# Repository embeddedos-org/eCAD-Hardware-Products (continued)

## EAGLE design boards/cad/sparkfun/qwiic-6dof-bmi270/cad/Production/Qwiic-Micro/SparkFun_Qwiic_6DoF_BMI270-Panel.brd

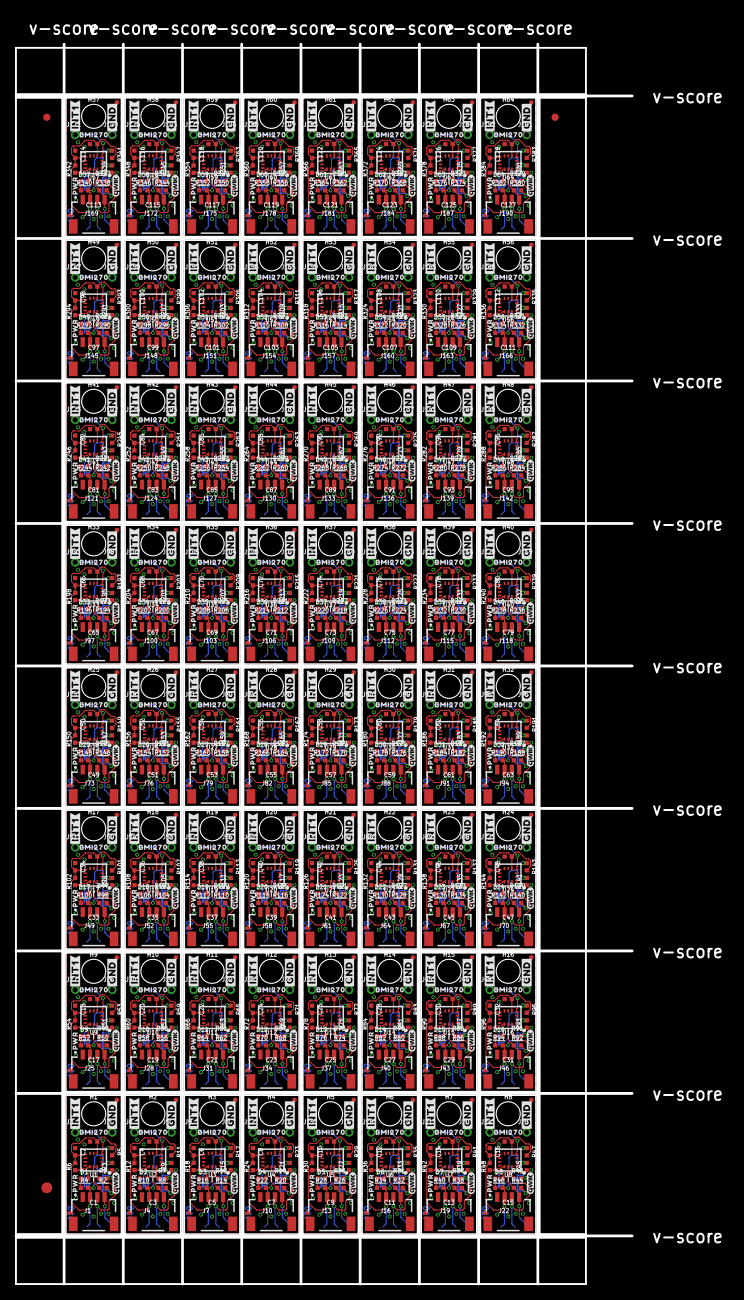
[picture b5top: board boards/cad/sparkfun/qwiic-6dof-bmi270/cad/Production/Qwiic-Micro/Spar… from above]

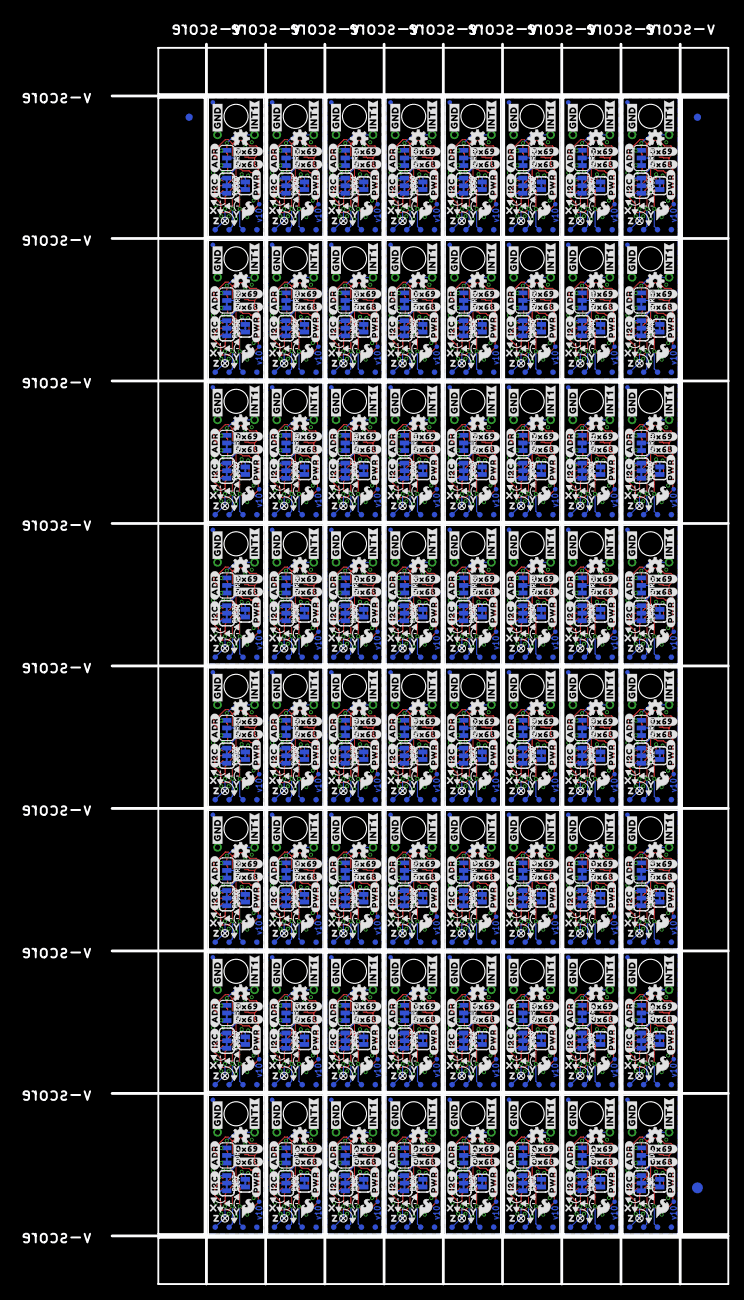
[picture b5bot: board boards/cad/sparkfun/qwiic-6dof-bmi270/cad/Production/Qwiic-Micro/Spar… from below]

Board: 2 copper layers, 84.6 x 170.2 mm, 2822 parts (1411 on the bottom side), 832 nets.

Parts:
ADR, ADR1, ADR2, ADR3, ADR4, ADR5, ADR6, ADR7, ADR8, ADR9, ADR10, ADR11, ADR12, ADR13, ADR14, ADR15, ADR16, ADR17, ADR18, ADR19, ADR20, ADR21, ADR22, ADR23, ADR24, ADR25, ADR26, ADR27, ADR28, ADR29, ADR30, ADR31, ADR32, ADR33, ADR34, ADR35, ADR36, ADR37, ADR38, ADR39, ADR40, ADR41, ADR42, ADR43, ADR44, ADR45, ADR46, ADR47, ADR48, ADR49, ADR50, ADR51, ADR52, ADR53, ADR54, ADR55, ADR56, ADR57, ADR58, ADR59, ADR60, ADR61, ADR62, ADR63: JUMPER-SMT_3_1-NC_TRACE_SILK; SMT-JUMPER_3_1-NC_TRACE_SILK
C1, C2, C3, C4, C5, C6, C7, C8, C9, C10, C11, C12, C13, C14, C15, C16, C17, C18, C19, C20, C21, C22, C23, C24, C25, C26, C27, C28, C29, C30, C31, C32, C33, C34, C35, C36, C37, C38, C39, C40, C41, C42, C43, C44, C45, C46, C47, C48, C49, C50, C51, C52, C53, C54, C55, C56, C57, C58, C59, C60, C61, C62, C63, C64, C65, C66, C67, C68, C69, C70, C71, C72, C73, C74, C75, C76, C77, C78, C79, C80, C81, C82, C83, C84, C85, C86, C87, C88, C89, C90, C91, C92, C93, C94, C95, C96, C97, C98, C99, C100, C101, C102, C103, C104, C105, C106, C107, C108, C109, C110, C111, C112, C113, C114, C115, C116, C117, C118, C119, C120, C121, C122, C123, C124, C125, C126, C127, C128: 0.1uF; 0402-TIGHT
D1, D2, D3, D4, D5, D6, D7, D8, D9, D10, D11, D12, D13, D14, D15, D16, D17, D18, D19, D20, D21, D22, D23, D24, D25, D26, D27, D28, D29, D30, D31, D32, D33, D34, D35, D36, D37, D38, D39, D40, D41, D42, D43, D44, D45, D46, D47, D48, D49, D50, D51, D52, D53, D54, D55, D56, D57, D58, D59, D60, D61, D62, D63, D64: RED; LED-0402
E$1, E$2, E$3, E$4: FIDUCIAL-1X2
E$5, E$6: FIDUCIAL-1.5X3
FD1, FD2, FD3, FD4, FD5, FD6, FD7, FD8, FD9, FD10, FD11, FD12, FD13, FD14, FD15, FD16, FD17, FD18, FD19, FD20, FD21, FD22, FD23, FD24, FD25, FD26, FD27, FD28, FD29, FD30, FD31, FD32, FD33, FD34, FD35, FD36, FD37, FD38, FD39, FD40, FD41, FD42, FD43, FD44, FD45, FD46, FD47, FD48, FD49, FD50, FD51, FD52, FD53, FD54, FD55, FD56, FD57, FD58, FD59, FD60, FD61, FD62, FD63, FD64, FD65, FD66, FD67, FD68, FD69, FD70, FD71, FD72, FD73, FD74, FD75, FD76, FD77, FD78, FD79, FD80, FD81, FD82, FD83, FD84, FD85, FD86, FD87, FD88, FD89, FD90, FD91, FD92, FD93, FD94, FD95, FD96, FD97, FD98, FD99, FD100, FD101, FD102, FD103, FD104, FD105, FD106, FD107, FD108, FD109, FD110, FD111, FD112, FD113, FD114, FD115, FD116, FD117, FD118, FD119, FD120, FD121, FD122, FD123, FD124, FD125, FD126, FD127, FD128, FD129, FD130, FD131, FD132, FD133, FD134, FD135, FD136, FD137, FD138, FD139, FD140, FD141, FD142, FD143, FD144, FD145, FD146, FD147, FD148, FD149, FD150, FD151, FD152, FD153, FD154, FD155, FD156, FD157, FD158, FD159, FD160, FD161, FD162, FD163, FD164, FD165, FD166, FD167, FD168, FD169, FD170, FD171, FD172, FD173, FD174, FD175, FD176, FD177, FD178, FD179, FD180, FD181, FD182, FD183, FD184, FD185, FD186, FD187, FD188, FD189, FD190, FD191, FD192, FD193, FD194, FD195, FD196, FD197, FD198, FD199, FD200, FD201, FD202, FD203, FD204, FD205, FD206, FD207, FD208, FD209, FD210, FD211, FD212, FD213, FD214, FD215, FD216, FD217, FD218, FD219, FD220, FD221, FD222, FD223, FD224, FD225, FD226, FD227, FD228, FD229, FD230, FD231, FD232, FD233, FD234, FD235, FD236, FD237, FD238, FD239, FD240, FD241, FD242, FD243, FD244, FD245, FD246, FD247, FD248, FD249, FD250, FD251, FD252, FD253, FD254, FD255, FD256: FIDUCIALUFIDUCIAL; FIDUCIAL-MICRO
FRAME1, FRAME2, FRAME3, FRAME4, FRAME5, FRAME6, FRAME7, FRAME8, FRAME9, FRAME10, FRAME11, FRAME12, FRAME13, FRAME14, FRAME15, FRAME16, FRAME17, FRAME18, FRAME19, FRAME20, FRAME21, FRAME22, FRAME23, FRAME24, FRAME25, FRAME26, FRAME27, FRAME28, FRAME29, FRAME30, FRAME31, FRAME32, FRAME33, FRAME34, FRAME35, FRAME36, FRAME37, FRAME38, FRAME39, FRAME40, FRAME41, FRAME42, FRAME43, FRAME44, FRAME45, FRAME46, FRAME47, FRAME48, FRAME49, FRAME50, FRAME51, FRAME52, FRAME53, FRAME54, FRAME55, FRAME56, FRAME57, FRAME58, FRAME59, FRAME60, FRAME61, FRAME62, FRAME63, FRAME64: FRAME-LETTER; CREATIVE_COMMONS
H1, H2, H3, H4, H5, H6, H7, H8, H9, H10, H11, H12, H13, H14, H15, H16, H17, H18, H19, H20, H21, H22, H23, H24, H25, H26, H27, H28, H29, H30, H31, H32, H33, H34, H35, H36, H37, H38, H39, H40, H41, H42, H43, H44, H45, H46, H47, H48, H49, H50, H51, H52, H53, H54, H55, H56, H57, H58, H59, H60, H61, H62, H63, H64: STAND-OFF
I2C, I2C1, I2C2, I2C3, I2C4, I2C5, I2C6, I2C7, I2C8, I2C9, I2C10, I2C11, I2C12, I2C13, I2C14, I2C15, I2C16, I2C17, I2C18, I2C19, I2C20, I2C21, I2C22, I2C23, I2C24, I2C25, I2C26, I2C27, I2C28, I2C29, I2C30, I2C31, I2C32, I2C33, I2C34, I2C35, I2C36, I2C37, I2C38, I2C39, I2C40, I2C41, I2C42, I2C43, I2C44, I2C45, I2C46, I2C47, I2C48, I2C49, I2C50, I2C51, I2C52, I2C53, I2C54, I2C55, I2C56, I2C57, I2C58, I2C59, I2C60, I2C61, I2C62, I2C63: JUMPER-SMT_3_2-NC_TRACE_SILK; SMT-JUMPER_3_2-NC_TRACE_SILK
J1, J4, J7, J10, J13, J16, J19, J22, J25, J28, J31, J34, J37, J40, J43, J46, J49, J52, J55, J58, J61, J64, J67, J70, J73, J76, J79, J82, J85, J88, J91, J94, J97, J100, J103, J106, J109, J112, J115, J118, J121, J124, J127, J130, J133, J136, J139, J142, J145, J148, J151, J154, J157, J160, J163, J166, J169, J172, J175, J178, J181, J184, J187, J190: QWIIC_RIGHT_ANGLE; JST04_1MM_RA
J2, J3, J5, J6, J8, J9, J11, J12, J14, J15, J17, J18, J20, J21, J23, J24, J26, J27, J29, J30, J32, J33, J35, J36, J38, J39, J41, J42, J44, J45, J47, J48, J50, J51, J53, J54, J56, J57, J59, J60, J62, J63, J65, J66, J68, J69, J71, J72, J74, J75, J77, J78, J80, J81, J83, J84, J86, J87, J89, J90, J92, J93, J95, J96, J98, J99, J101, J102, J104, J105, J107, J108, J110, J111, J113, J114, J116, J117, J119, J120, J122, J123, J125, J126, J128, J129, J131, J132, J134, J135, J137, J138, J140, J141, J143, J144, J146, J147, J149, J150, J152, J153, J155, J156, J158, J159, J161, J162, J164, J165, J167, J168, J170, J171, J173, J174, J176, J177, J179, J180, J182, J183, J185, J186, J188, J189, J191, J192: 1X01_1MM_NO_SILK
LOGO1, LOGO4, LOGO7, LOGO10, LOGO13, LOGO16, LOGO19, LOGO22, LOGO25, LOGO28, LOGO31, LOGO34, LOGO37, LOGO40, LOGO43, LOGO46, LOGO49, LOGO52, LOGO55, LOGO58, LOGO61, LOGO64, LOGO67, LOGO70, LOGO73, LOGO76, LOGO79, LOGO82, LOGO85, LOGO88, LOGO91, LOGO94, LOGO97, LOGO100, LOGO103, LOGO106, LOGO109, LOGO112, LOGO115, LOGO118, LOGO121, LOGO124, LOGO127, LOGO130, LOGO133, LOGO136, LOGO139, LOGO142, LOGO145, LOGO148, LOGO151, LOGO154, LOGO157, LOGO160, LOGO163, LOGO166, LOGO169, LOGO172, LOGO175, LOGO178, LOGO181, LOGO184, LOGO187, LOGO190: SFE_LOGO_NAME_FLAMEBLANK; BLANK
LOGO2, LOGO5, LOGO8, LOGO11, LOGO14, LOGO17, LOGO20, LOGO23, LOGO26, LOGO29, LOGO32, LOGO35, LOGO38, LOGO41, LOGO44, LOGO47, LOGO50, LOGO53, LOGO56, LOGO59, LOGO62, LOGO65, LOGO68, LOGO71, LOGO74, LOGO77, LOGO80, LOGO83, LOGO86, LOGO89, LOGO92, LOGO95, LOGO98, LOGO101, LOGO104, LOGO107, LOGO110, LOGO113, LOGO116, LOGO119, LOGO122, LOGO125, LOGO128, LOGO131, LOGO134, LOGO137, LOGO140, LOGO143, LOGO146, LOGO149, LOGO152, LOGO155, LOGO158, LOGO161, LOGO164, LOGO167, LOGO170, LOGO173, LOGO176, LOGO179, LOGO182, LOGO185, LOGO188, LOGO191: QWIIC_LOGO_3MM; QWIIC_3MM
LOGO3, LOGO6, LOGO9, LOGO12, LOGO15, LOGO18, LOGO21, LOGO24, LOGO27, LOGO30, LOGO33, LOGO36, LOGO39, LOGO42, LOGO45, LOGO48, LOGO51, LOGO54, LOGO57, LOGO60, LOGO63, LOGO66, LOGO69, LOGO72, LOGO75, LOGO78, LOGO81, LOGO84, LOGO87, LOGO90, LOGO93, LOGO96, LOGO99, LOGO102, LOGO105, LOGO108, LOGO111, LOGO114, LOGO117, LOGO120, LOGO123, LOGO126, LOGO129, LOGO132, LOGO135, LOGO138, LOGO141, LOGO144, LOGO147, LOGO150, LOGO153, LOGO156, LOGO159, LOGO162, LOGO165, LOGO168, LOGO171, LOGO174, LOGO177, LOGO180, LOGO183, LOGO186, LOGO189, LOGO192: OSHW-LOGOMINI; OSHW-LOGO-MINI
PWR, PWR1, PWR2, PWR3, PWR4, PWR5, PWR6, PWR7, PWR8, PWR9, PWR10, PWR11, PWR12, PWR13, PWR14, PWR15, PWR16, PWR17, PWR18, PWR19, PWR20, PWR21, PWR22, PWR23, PWR24, PWR25, PWR26, PWR27, PWR28, PWR29, PWR30, PWR31, PWR32, PWR33, PWR34, PWR35, PWR36, PWR37, PWR38, PWR39, PWR40, PWR41, PWR42, PWR43, PWR44, PWR45, PWR46, PWR47, PWR48, PWR49, PWR50, PWR51, PWR52, PWR53, PWR54, PWR55, PWR56, PWR57, PWR58, PWR59, PWR60, PWR61, PWR62, PWR63: JUMPER-SMT_2_NC_TRACE_SILK; SMT-JUMPER_2_NC_TRACE_SILK
R1, R2, R7, R8, R13, R14, R19, R20, R25, R26, R31, R32, R37, R38, R43, R44, R49, R50, R55, R56, R61, R62, R67, R68, R73, R74, R79, R80, R85, R86, R91, R92, R97, R98, R103, R104, R109, R110, R115, R116, R121, R122, R127, R128, R133, R134, R139, R140, R145, R146, R151, R152, R157, R158, R163, R164, R169, R170, R175, R176, R181, R182, R187, R188, R193, R194, R199, R200, R205, R206, R211, R212, R217, R218, R223, R224, R229, R230, R235, R236, R241, R242, R247, R248, R253, R254, R259, R260, R265, R266, R271, R272, R277, R278, R283, R284, R289, R290, R295, R296, R301, R302, R307, R308, R313, R314, R319, R320, R325, R326, R331, R332, R337, R338, R343, R344, R349, R350, R355, R356, R361, R362, R367, R368, R373, R374, R379, R380: 2.2k; 0402-TIGHT
R3, R5, R6, R9, R11, R12, R15, R17, R18, R21, R23, R24, R27, R29, R30, R33, R35, R36, R39, R41, R42, R45, R47, R48, R51, R53, R54, R57, R59, R60, R63, R65, R66, R69, R71, R72, R75, R77, R78, R81, R83, R84, R87, R89, R90, R93, R95, R96, R99, R101, R102, R105, R107, R108, R111, R113, R114, R117, R119, R120, R123, R125, R126, R129, R131, R132, R135, R137, R138, R141, R143, R144, R147, R149, R150, R153, R155, R156, R159, R161, R162, R165, R167, R168, R171, R173, R174, R177, R179, R180, R183, R185, R186, R189, R191, R192, R195, R197, R198, R201, R203, R204, R207, R209, R210, R213, R215, R216, R219, R221, R222, R225, R227, R228, R231, R233, R234, R237, R239, R240, R243, R245, R246, R249, R251, R252, R255, R257, R258, R261, R263, R264, R267, R269, R270, R273, R275, R276, R279, R281, R282, R285, R287, R288, R291, R293, R294, R297, R299, R300, R303, R305, R306, R309, R311, R312, R315, R317, R318, R321, R323, R324, R327, R329, R330, R333, R335, R336, R339, R341, R342, R345, R347, R348, R351, R353, R354, R357, R359, R360, R363, R365, R366, R369, R371, R372, R375, R377, R378, R381, R383, R384: 100k; 0402-TIGHT
R4, R10, R16, R22, R28, R34, R40, R46, R52, R58, R64, R70, R76, R82, R88, R94, R100, R106, R112, R118, R124, R130, R136, R142, R148, R154, R160, R166, R172, R178, R184, R190, R196, R202, R208, R214, R220, R226, R232, R238, R244, R250, R256, R262, R268, R274, R280, R286, R292, R298, R304, R310, R316, R322, R328, R334, R340, R346, R352, R358, R364, R370, R376, R382: 4.7k; 0402-TIGHT
TP1, TP2, TP3, TP4, TP5, TP6, TP7, TP8, TP9, TP10, TP11, TP12, TP13, TP14, TP15, TP16, TP17, TP18, TP19, TP20, TP21, TP22, TP23, TP24, TP25, TP26, TP27, TP28, TP29, TP30, TP31, TP32, TP33, TP34, TP35, TP36, TP37, TP38, TP39, TP40, TP41, TP42, TP43, TP44, TP45, TP46, TP47, TP48, TP49, TP50, TP51, TP52, TP53, TP54, TP55, TP56, TP57, TP58, TP59, TP60, TP61, TP62, TP63, TP64, TP65, TP66, TP67, TP68, TP69, TP70, TP71, TP72, TP73, TP74, TP75, TP76, TP77, TP78, TP79, TP80, TP81, TP82, TP83, TP84, TP85, TP86, TP87, TP88, TP89, TP90, TP91, TP92, TP93, TP94, TP95, TP96, TP97, TP98, TP99, TP100, TP101, TP102, TP103, TP104, TP105, TP106, TP107, TP108, TP109, TP110, TP111, TP112, TP113, TP114, TP115, TP116, TP117, TP118, TP119, TP120, TP121, TP122, TP123, TP124, TP125, TP126, TP127, TP128, TP129, TP130, TP131, TP132, TP133, TP134, TP135, TP136, TP137, TP138, TP139, TP140, TP141, TP142, TP143, TP144, TP145, TP146, TP147, TP148, TP149, TP150, TP151, TP152, TP153, TP154, TP155, TP156, TP157, TP158, TP159, TP160, TP161, TP162, TP163, TP164, TP165, TP166, TP167, TP168, TP169, TP170, TP171, TP172, TP173, TP174, TP175, TP176, TP177, TP178, TP179, TP180, TP181, TP182, TP183, TP184, TP185, TP186, TP187, TP188, TP189, TP190, TP191, TP192, TP193, TP194, TP195, TP196, TP197, TP198, TP199, TP200, TP201, TP202, TP203, TP204, TP205, TP206, TP207, TP208, TP209, TP210, TP211, TP212, TP213, TP214, TP215, TP216, TP217, TP218, TP219, TP220, TP221, TP222, TP223, TP224, TP225, TP226, TP227, TP228, TP229, TP230, TP231, TP232, TP233, TP234, TP235, TP236, TP237, TP238, TP239, TP240, TP241, TP242, TP243, TP244, TP245, TP246, TP247, TP248, TP249, TP250, TP251, TP252, TP253, TP254, TP255, TP256: TEST-POINT3; PAD.03X.03
U1, U2, U3, U4, U5, U6, U7, U8, U9, U10, U11, U12, U13, U14, U15, U16, U17, U18, U19, U20, U21, U22, U23, U24, U25, U26, U27, U28, U29, U30, U31, U32, U33, U34, U35, U36, U37, U38, U39, U40, U41, U42, U43, U44, U45, U46, U47, U48, U49, U50, U51, U52, U53, U54, U55, U56, U57, U58, U59, U60, U61, U62, U63, U64: BMI270
U$1, U$10, U$27, U$43, U$58, U$73, U$91, U$106, U$121, U$136, U$151, U$166, U$181, U$196, U$211, U$226, U$241, U$256, U$271, U$286, U$301, U$316, U$331, U$346, U$361, U$376, U$391, U$406, U$421, U$436, U$451, U$466, U$481, U$496, U$511, U$526, U$541, U$556, U$571, U$586, U$601, U$616, U$631, U$646, U$661, U$676, U$691, U$706, U$721, U$736, U$751, U$766, U$781, U$796, U$811, U$826, U$841, U$856, U$871, U$886, U$901, U$916, U$931, U$946: #I2C#0
U$2, U$7, U$22, U$23, U$38, U$39, U$53, U$54, U$68, U$69, U$86, U$87, U$101, U$102, U$116, U$117, U$131, U$132, U$146, U$147, U$161, U$162, U$176, U$177, U$191, U$192, U$206, U$207, U$221, U$222, U$236, U$237, U$251, U$252, U$266, U$267, U$281, U$282, U$296, U$297, U$311, U$312, U$326, U$327, U$341, U$342, U$356, U$357, U$371, U$372, U$386, U$387, U$401, U$402, U$416, U$417, U$431, U$432, U$446, U$447, U$461, U$462, U$476, U$477, U$491, U$492, U$506, U$507, U$521, U$522, U$536, U$537, U$551, U$552, U$566, U$567, U$581, U$582, U$596, U$597, U$611, U$612, U$626, U$627, U$641, U$642, U$656, U$657, U$671, U$672, U$686, U$687, U$701, U$702, U$716, U$717, U$731, U$732, U$746, U$747, U$761, U$762, U$776, U$777, U$791, U$792, U$806, U$807, U$821, U$822, U$836, U$837, U$851, U$852, U$866, U$867, U$881, U$882, U$896, U$897, U$911, U$912, U$926, U$927, U$941, U$942, U$956, U$957: #GND#0
U$3, U$26, U$42, U$57, U$72, U$90, U$105, U$120, U$135, U$150, U$165, U$180, U$195, U$210, U$225, U$240, U$255, U$270, U$285, U$300, U$315, U$330, U$345, U$360, U$375, U$390, U$405, U$420, U$435, U$450, U$465, U$480, U$495, U$510, U$525, U$540, U$555, U$570, U$585, U$600, U$615, U$630, U$645, U$660, U$675, U$690, U$705, U$720, U$735, U$750, U$765, U$780, U$795, U$810, U$825, U$840, U$855, U$870, U$885, U$900, U$915, U$930, U$945, U$960: SFE_LOGO_FLAME_.1
U$4, U$11, U$28, U$44, U$59, U$74, U$92, U$107, U$122, U$137, U$152, U$167, U$182, U$197, U$212, U$227, U$242, U$257, U$272, U$287, U$302, U$317, U$332, U$347, U$362, U$377, U$392, U$407, U$422, U$437, U$452, U$467, U$482, U$497, U$512, U$527, U$542, U$557, U$572, U$587, U$602, U$617, U$632, U$647, U$662, U$677, U$692, U$707, U$722, U$737, U$752, U$767, U$782, U$797, U$812, U$827, U$842, U$857, U$872, U$887, U$902, U$917, U$932, U$947: #PWR#0
U$5, U$12, U$29, U$45, U$60, U$75, U$93, U$108, U$123, U$138, U$153, U$168, U$183, U$198, U$213, U$228, U$243, U$258, U$273, U$288, U$303, U$318, U$333, U$348, U$363, U$378, U$393, U$408, U$423, U$438, U$453, U$468, U$483, U$498, U$513, U$528, U$543, U$558, U$573, U$588, U$603, U$618, U$633, U$648, U$663, U$678, U$693, U$708, U$723, U$738, U$753, U$768, U$783, U$798, U$813, U$828, U$843, U$858, U$873, U$888, U$903, U$918, U$933, U$948: #ADR#0
U$6, U$13, U$30, U$46, U$61, U$76, U$94, U$109, U$124, U$139, U$154, U$169, U$184, U$199, U$214, U$229, U$244, U$259, U$274, U$289, U$304, U$319, U$334, U$349, U$364, U$379, U$394, U$409, U$424, U$439, U$454, U$469, U$484, U$499, U$514, U$529, U$544, U$559, U$574, U$589, U$604, U$619, U$634, U$649, U$664, U$679, U$694, U$709, U$724, U$739, U$754, U$769, U$784, U$799, U$814, U$829, U$844, U$859, U$874, U$889, U$904, U$919, U$934, U$949: #0X68#0
U$8, U$9, U$24, U$25, U$40, U$41, U$55, U$56, U$70, U$71, U$88, U$89, U$103, U$104, U$118, U$119, U$133, U$134, U$148, U$149, U$163, U$164, U$178, U$179, U$193, U$194, U$208, U$209, U$223, U$224, U$238, U$239, U$253, U$254, U$268, U$269, U$283, U$284, U$298, U$299, U$313, U$314, U$328, U$329, U$343, U$344, U$358, U$359, U$373, U$374, U$388, U$389, U$403, U$404, U$418, U$419, U$433, U$434, U$448, U$449, U$463, U$464, U$478, U$479, U$493, U$494, U$508, U$509, U$523, U$524, U$538, U$539, U$553, U$554, U$568, U$569, U$583, U$584, U$598, U$599, U$613, U$614, U$628, U$629, U$643, U$644, U$658, U$659, U$673, U$674, U$688, U$689, U$703, U$704, U$718, U$719, U$733, U$734, U$748, U$749, U$763, U$764, U$778, U$779, U$793, U$794, U$808, U$809, U$823, U$824, U$838, U$839, U$853, U$854, U$868, U$869, U$883, U$884, U$898, U$899, U$913, U$914, U$928, U$929, U$943, U$944, U$958, U$959: #INT1#0
U$14, U$18, U$31, U$47, U$62, U$77, U$95, U$110, U$125, U$140, U$155, U$170, U$185, U$200, U$215, U$230, U$245, U$260, U$275, U$290, U$305, U$320, U$335, U$350, U$365, U$380, U$395, U$410, U$425, U$440, U$455, U$470, U$485, U$500, U$515, U$530, U$545, U$560, U$575, U$590, U$605, U$620, U$635, U$650, U$665, U$680, U$695, U$710, U$725, U$740, U$755, U$770, U$785, U$800, U$815, U$830, U$845, U$860, U$875, U$890, U$905, U$920, U$935, U$950: #0X69#0
U$15, U$21, U$32, U$48, U$63, U$78, U$96, U$111, U$126, U$141, U$156, U$171, U$186, U$201, U$216, U$231, U$246, U$261, U$276, U$291, U$306, U$321, U$336, U$351, U$366, U$381, U$396, U$411, U$426, U$441, U$456, U$471, U$486, U$501, U$516, U$531, U$546, U$561, U$576, U$591, U$606, U$621, U$636, U$651, U$666, U$681, U$696, U$711, U$726, U$741, U$756, U$771, U$786, U$801, U$816, U$831, U$846, U$861, U$876, U$891, U$906, U$921, U$936, U$951: BMI2700
U$16, U$33, U$49, U$64, U$79, U$82, U$97, U$112, U$127, U$142, U$157, U$172, U$187, U$202, U$217, U$232, U$247, U$262, U$277, U$292, U$307, U$322, U$337, U$352, U$367, U$382, U$397, U$412, U$427, U$442, U$457, U$472, U$487, U$502, U$517, U$532, U$547, U$562, U$577, U$592, U$607, U$622, U$637, U$652, U$667, U$682, U$697, U$712, U$727, U$742, U$757, U$772, U$787, U$802, U$817, U$832, U$847, U$862, U$877, U$892, U$907, U$922, U$937, U$952: X0
U$17, U$35, U$50, U$65, U$80, U$83, U$98, U$113, U$128, U$143, U$158, U$173, U$188, U$203, U$218, U$233, U$248, U$263, U$278, U$293, U$308, U$323, U$338, U$353, U$368, U$383, U$398, U$413, U$428, U$443, U$458, U$473, U$488, U$503, U$518, U$533, U$548, U$563, U$578, U$593, U$608, U$623, U$638, U$653, U$668, U$683, U$698, U$713, U$728, U$743, U$758, U$773, U$788, U$803, U$818, U$833, U$848, U$863, U$878, U$893, U$908, U$923, U$938, U$953: Y0
U$19, U$36, U$51, U$66, U$81, U$84, U$99, U$114, U$129, U$144, U$159, U$174, U$189, U$204, U$219, U$234, U$249, U$264, U$279, U$294, U$309, U$324, U$339, U$354, U$369, U$384, U$399, U$414, U$429, U$444, U$459, U$474, U$489, U$504, U$519, U$534, U$549, U$564, U$579, U$594, U$609, U$624, U$639, U$654, U$669, U$684, U$699, U$714, U$729, U$744, U$759, U$774, U$789, U$804, U$819, U$834, U$849, U$864, U$879, U$894, U$909, U$924, U$939, U$954: Z0
U$20, U$34, U$37, U$52, U$67, U$85, U$100, U$115, U$130, U$145, U$160, U$175, U$190, U$205, U$220, U$235, U$250, U$265, U$280, U$295, U$310, U$325, U$340, U$355, U$370, U$385, U$400, U$415, U$430, U$445, U$460, U$475, U$490, U$505, U$520, U$535, U$550, U$565, U$580, U$595, U$610, U$625, U$640, U$655, U$670, U$685, U$700, U$715, U$730, U$745, U$760, U$775, U$790, U$805, U$820, U$835, U$850, U$865, U$880, U$895, U$910, U$925, U$940, U$955: PWR0

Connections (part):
3.3V: C1.2, C2.2, I2C.2, J1.2, R4.2, R5.2, R6.2, TP3.1, U1.5, U1.8
3.3V1: C3.2, C4.2, I2C1.2, J4.2, R10.2, R11.2, R12.2, TP7.1, U2.5, U2.8
3.3V2: C5.2, C6.2, I2C2.2, J7.2, R16.2, R17.2, R18.2, TP11.1, U3.5, U3.8
3.3V3: C7.2, C8.2, I2C3.2, J10.2, R22.2, R23.2, R24.2, TP15.1, U4.5, U4.8
3.3V4: C9.2, C10.2, I2C4.2, J13.2, R28.2, R29.2, R30.2, TP19.1, U5.5, U5.8
3.3V5: C11.2, C12.2, I2C5.2, J16.2, R34.2, R35.2, R36.2, TP23.1, U6.5, U6.8
3.3V6: C13.2, C14.2, I2C6.2, J19.2, R40.2, R41.2, R42.2, TP27.1, U7.5, U7.8
3.3V7: C15.2, C16.2, I2C7.2, J22.2, R46.2, R47.2, R48.2, TP31.1, U8.5, U8.8
3.3V8: C17.2, C18.2, I2C8.2, J25.2, R52.2, R53.2, R54.2, TP35.1, U9.5, U9.8
3.3V9: C19.2, C20.2, I2C9.2, J28.2, R58.2, R59.2, R60.2, TP39.1, U10.5, U10.8
3.3V10: C21.2, C22.2, I2C10.2, J31.2, R64.2, R65.2, R66.2, TP43.1, U11.5, U11.8
3.3V11: C23.2, C24.2, I2C11.2, J34.2, R70.2, R71.2, R72.2, TP47.1, U12.5, U12.8
3.3V12: C25.2, C26.2, I2C12.2, J37.2, R76.2, R77.2, R78.2, TP51.1, U13.5, U13.8
3.3V13: C27.2, C28.2, I2C13.2, J40.2, R82.2, R83.2, R84.2, TP55.1, U14.5, U14.8
3.3V14: C29.2, C30.2, I2C14.2, J43.2, R88.2, R89.2, R90.2, TP59.1, U15.5, U15.8
3.3V15: C31.2, C32.2, I2C15.2, J46.2, R94.2, R95.2, R96.2, TP63.1, U16.5, U16.8
3.3V16: C33.2, C34.2, I2C16.2, J49.2, R100.2, R101.2, R102.2, TP67.1, U17.5, U17.8
3.3V17: C35.2, C36.2, I2C17.2, J52.2, R106.2, R107.2, R108.2, TP71.1, U18.5, U18.8
3.3V18: C37.2, C38.2, I2C18.2, J55.2, R112.2, R113.2, R114.2, TP75.1, U19.5, U19.8
3.3V19: C39.2, C40.2, I2C19.2, J58.2, R118.2, R119.2, R120.2, TP79.1, U20.5, U20.8
3.3V20: C41.2, C42.2, I2C20.2, J61.2, R124.2, R125.2, R126.2, TP83.1, U21.5, U21.8
3.3V21: C43.2, C44.2, I2C21.2, J64.2, R130.2, R131.2, R132.2, TP87.1, U22.5, U22.8
3.3V22: C45.2, C46.2, I2C22.2, J67.2, R136.2, R137.2, R138.2, TP91.1, U23.5, U23.8
3.3V23: C47.2, C48.2, I2C23.2, J70.2, R142.2, R143.2, R144.2, TP95.1, U24.5, U24.8
3.3V24: C49.2, C50.2, I2C24.2, J73.2, R148.2, R149.2, R150.2, TP99.1, U25.5, U25.8
3.3V25: C51.2, C52.2, I2C25.2, J76.2, R154.2, R155.2, R156.2, TP103.1, U26.5, U26.8
3.3V26: C53.2, C54.2, I2C26.2, J79.2, R160.2, R161.2, R162.2, TP107.1, U27.5, U27.8
3.3V27: C55.2, C56.2, I2C27.2, J82.2, R166.2, R167.2, R168.2, TP111.1, U28.5, U28.8
3.3V28: C57.2, C58.2, I2C28.2, J85.2, R172.2, R173.2, R174.2, TP115.1, U29.5, U29.8
3.3V29: C59.2, C60.2, I2C29.2, J88.2, R178.2, R179.2, R180.2, TP119.1, U30.5, U30.8
3.3V30: C61.2, C62.2, I2C30.2, J91.2, R184.2, R185.2, R186.2, TP123.1, U31.5, U31.8
3.3V31: C63.2, C64.2, I2C31.2, J94.2, R190.2, R191.2, R192.2, TP127.1, U32.5, U32.8
3.3V32: C65.2, C66.2, I2C32.2, J97.2, R196.2, R197.2, R198.2, TP131.1, U33.5, U33.8
3.3V33: C67.2, C68.2, I2C33.2, J100.2, R202.2, R203.2, R204.2, TP135.1, U34.5, U34.8
3.3V34: C69.2, C70.2, I2C34.2, J103.2, R208.2, R209.2, R210.2, TP139.1, U35.5, U35.8
3.3V35: C71.2, C72.2, I2C35.2, J106.2, R214.2, R215.2, R216.2, TP143.1, U36.5, U36.8
3.3V36: C73.2, C74.2, I2C36.2, J109.2, R220.2, R221.2, R222.2, TP147.1, U37.5, U37.8
3.3V37: C75.2, C76.2, I2C37.2, J112.2, R226.2, R227.2, R228.2, TP151.1, U38.5, U38.8
3.3V38: C77.2, C78.2, I2C38.2, J115.2, R232.2, R233.2, R234.2, TP155.1, U39.5, U39.8
3.3V39: C79.2, C80.2, I2C39.2, J118.2, R238.2, R239.2, R240.2, TP159.1, U40.5, U40.8
3.3V40: C81.2, C82.2, I2C40.2, J121.2, R244.2, R245.2, R246.2, TP163.1, U41.5, U41.8
3.3V41: C83.2, C84.2, I2C41.2, J124.2, R250.2, R251.2, R252.2, TP167.1, U42.5, U42.8
3.3V42: C85.2, C86.2, I2C42.2, J127.2, R256.2, R257.2, R258.2, TP171.1, U43.5, U43.8
3.3V43: C87.2, C88.2, I2C43.2, J130.2, R262.2, R263.2, R264.2, TP175.1, U44.5, U44.8
3.3V44: C89.2, C90.2, I2C44.2, J133.2, R268.2, R269.2, R270.2, TP179.1, U45.5, U45.8
3.3V45: C91.2, C92.2, I2C45.2, J136.2, R274.2, R275.2, R276.2, TP183.1, U46.5, U46.8
3.3V46: C93.2, C94.2, I2C46.2, J139.2, R280.2, R281.2, R282.2, TP187.1, U47.5, U47.8
3.3V47: C95.2, C96.2, I2C47.2, J142.2, R286.2, R287.2, R288.2, TP191.1, U48.5, U48.8
3.3V48: C97.2, C98.2, I2C48.2, J145.2, R292.2, R293.2, R294.2, TP195.1, U49.5, U49.8
3.3V49: C99.2, C100.2, I2C49.2, J148.2, R298.2, R299.2, R300.2, TP199.1, U50.5, U50.8
3.3V50: C101.2, C102.2, I2C50.2, J151.2, R304.2, R305.2, R306.2, TP203.1, U51.5, U51.8
3.3V51: C103.2, C104.2, I2C51.2, J154.2, R310.2, R311.2, R312.2, TP207.1, U52.5, U52.8
3.3V52: C105.2, C106.2, I2C52.2, J157.2, R316.2, R317.2, R318.2, TP211.1, U53.5, U53.8
3.3V53: C107.2, C108.2, I2C53.2, J160.2, R322.2, R323.2, R324.2, TP215.1, U54.5, U54.8
3.3V54: C109.2, C110.2, I2C54.2, J163.2, R328.2, R329.2, R330.2, TP219.1, U55.5, U55.8
3.3V55: C111.2, C112.2, I2C55.2, J166.2, R334.2, R335.2, R336.2, TP223.1, U56.5, U56.8
3.3V56: C113.2, C114.2, I2C56.2, J169.2, R340.2, R341.2, R342.2, TP227.1, U57.5, U57.8
3.3V57: C115.2, C116.2, I2C57.2, J172.2, R346.2, R347.2, R348.2, TP231.1, U58.5, U58.8
3.3V58: C117.2, C118.2, I2C58.2, J175.2, R352.2, R353.2, R354.2, TP235.1, U59.5, U59.8
3.3V59: C119.2, C120.2, I2C59.2, J178.2, R358.2, R359.2, R360.2, TP239.1, U60.5, U60.8
3.3V60: C121.2, C122.2, I2C60.2, J181.2, R364.2, R365.2, R366.2, TP243.1, U61.5, U61.8
3.3V61: C123.2, C124.2, I2C61.2, J184.2, R370.2, R371.2, R372.2, TP247.1, U62.5, U62.8
3.3V62: C125.2, C126.2, I2C62.2, J187.2, R376.2, R377.2, R378.2, TP251.1, U63.5, U63.8
3.3V63: C127.2, C128.2, I2C63.2, J190.2, R382.2, R383.2, R384.2, TP255.1, U64.5, U64.8
ADR: ADR.2, U1.1
ADR1: ADR1.2, U2.1
ADR2: ADR2.2, U3.1
ADR3: ADR3.2, U4.1
ADR4: ADR4.2, U5.1
ADR5: ADR5.2, U6.1
ADR6: ADR6.2, U7.1
ADR7: ADR7.2, U8.1
ADR8: ADR8.2, U9.1
ADR9: ADR9.2, U10.1
ADR10: ADR10.2, U11.1
ADR11: ADR11.2, U12.1
ADR12: ADR12.2, U13.1
ADR13: ADR13.2, U14.1
ADR14: ADR14.2, U15.1
ADR15: ADR15.2, U16.1
ADR16: ADR16.2, U17.1
ADR17: ADR17.2, U18.1
ADR18: ADR18.2, U19.1
ADR19: ADR19.2, U20.1
ADR20: ADR20.2, U21.1
ADR21: ADR21.2, U22.1
ADR22: ADR22.2, U23.1
ADR23: ADR23.2, U24.1
ADR24: ADR24.2, U25.1
ADR25: ADR25.2, U26.1
ADR26: ADR26.2, U27.1
ADR27: ADR27.2, U28.1
ADR28: ADR28.2, U29.1
ADR29: ADR29.2, U30.1
ADR30: ADR30.2, U31.1
ADR31: ADR31.2, U32.1
ADR32: ADR32.2, U33.1
ADR33: ADR33.2, U34.1
ADR34: ADR34.2, U35.1
ADR35: ADR35.2, U36.1
ADR36: ADR36.2, U37.1
ADR37: ADR37.2, U38.1
ADR38: ADR38.2, U39.1
ADR39: ADR39.2, U40.1
ADR40: ADR40.2, U41.1
ADR41: ADR41.2, U42.1
ADR42: ADR42.2, U43.1
ADR43: ADR43.2, U44.1
ADR44: ADR44.2, U45.1
ADR45: ADR45.2, U46.1
ADR46: ADR46.2, U47.1
ADR47: ADR47.2, U48.1
ADR48: ADR48.2, U49.1
ADR49: ADR49.2, U50.1
ADR50: ADR50.2, U51.1
ADR51: ADR51.2, U52.1
ADR52: ADR52.2, U53.1
ADR53: ADR53.2, U54.1
ADR54: ADR54.2, U55.1
ADR55: ADR55.2, U56.1
ADR56: ADR56.2, U57.1
ADR57: ADR57.2, U58.1
ADR58: ADR58.2, U59.1
ADR59: ADR59.2, U60.1
ADR60: ADR60.2, U61.1
ADR61: ADR61.2, U62.1
ADR62: ADR62.2, U63.1
ADR63: ADR63.2, U64.1
GND: C1.1, C2.1, J1.1, J2.1, PWR.1, R3.1, TP4.1, U1.6, U1.7
GND1: C3.1, C4.1, J4.1, J5.1, PWR1.1, R9.1, TP8.1, U2.6, U2.7
GND2: C5.1, C6.1, J7.1, J8.1, PWR2.1, R15.1, TP12.1, U3.6, U3.7
GND3: C7.1, C8.1, J10.1, J11.1, PWR3.1, R21.1, TP16.1, U4.6, U4.7
GND4: C9.1, C10.1, J13.1, J14.1, PWR4.1, R27.1, TP20.1, U5.6, U5.7
GND5: C11.1, C12.1, J16.1, J17.1, PWR5.1, R33.1, TP24.1, U6.6, U6.7
GND6: C13.1, C14.1, J19.1, J20.1, PWR6.1, R39.1, TP28.1, U7.6, U7.7
GND7: C15.1, C16.1, J22.1, J23.1, PWR7.1, R45.1, TP32.1, U8.6, U8.7
GND8: C17.1, C18.1, J25.1, J26.1, PWR8.1, R51.1, TP36.1, U9.6, U9.7
GND9: C19.1, C20.1, J28.1, J29.1, PWR9.1, R57.1, TP40.1, U10.6, U10.7
GND10: C21.1, C22.1, J31.1, J32.1, PWR10.1, R63.1, TP44.1, U11.6, U11.7
GND11: C23.1, C24.1, J34.1, J35.1, PWR11.1, R69.1, TP48.1, U12.6, U12.7
GND12: C25.1, C26.1, J37.1, J38.1, PWR12.1, R75.1, TP52.1, U13.6, U13.7
GND13: C27.1, C28.1, J40.1, J41.1, PWR13.1, R81.1, TP56.1, U14.6, U14.7
GND14: C29.1, C30.1, J43.1, J44.1, PWR14.1, R87.1, TP60.1, U15.6, U15.7
GND15: C31.1, C32.1, J46.1, J47.1, PWR15.1, R93.1, TP64.1, U16.6, U16.7
GND16: C33.1, C34.1, J49.1, J50.1, PWR16.1, R99.1, TP68.1, U17.6, U17.7
GND17: C35.1, C36.1, J52.1, J53.1, PWR17.1, R105.1, TP72.1, U18.6, U18.7
GND18: C37.1, C38.1, J55.1, J56.1, PWR18.1, R111.1, TP76.1, U19.6, U19.7
GND19: C39.1, C40.1, J58.1, J59.1, PWR19.1, R117.1, TP80.1, U20.6, U20.7
GND20: C41.1, C42.1, J61.1, J62.1, PWR20.1, R123.1, TP84.1, U21.6, U21.7
GND21: C43.1, C44.1, J64.1, J65.1, PWR21.1, R129.1, TP88.1, U22.6, U22.7
GND22: C45.1, C46.1, J67.1, J68.1, PWR22.1, R135.1, TP92.1, U23.6, U23.7
GND23: C47.1, C48.1, J70.1, J71.1, PWR23.1, R141.1, TP96.1, U24.6, U24.7
GND24: C49.1, C50.1, J73.1, J74.1, PWR24.1, R147.1, TP100.1, U25.6, U25.7
GND25: C51.1, C52.1, J76.1, J77.1, PWR25.1, R153.1, TP104.1, U26.6, U26.7
GND26: C53.1, C54.1, J79.1, J80.1, PWR26.1, R159.1, TP108.1, U27.6, U27.7
GND27: C55.1, C56.1, J82.1, J83.1, PWR27.1, R165.1, TP112.1, U28.6, U28.7
GND28: C57.1, C58.1, J85.1, J86.1, PWR28.1, R171.1, TP116.1, U29.6, U29.7
GND29: C59.1, C60.1, J88.1, J89.1, PWR29.1, R177.1, TP120.1, U30.6, U30.7
GND30: C61.1, C62.1, J91.1, J92.1, PWR30.1, R183.1, TP124.1, U31.6, U31.7
GND31: C63.1, C64.1, J94.1, J95.1, PWR31.1, R189.1, TP128.1, U32.6, U32.7
GND32: C65.1, C66.1, J97.1, J98.1, PWR32.1, R195.1, TP132.1, U33.6, U33.7
GND33: C67.1, C68.1, J100.1, J101.1, PWR33.1, R201.1, TP136.1, U34.6, U34.7
GND34: C69.1, C70.1, J103.1, J104.1, PWR34.1, R207.1, TP140.1, U35.6, U35.7
GND35: C71.1, C72.1, J106.1, J107.1, PWR35.1, R213.1, TP144.1, U36.6, U36.7
GND36: C73.1, C74.1, J109.1, J110.1, PWR36.1, R219.1, TP148.1, U37.6, U37.7
GND37: C75.1, C76.1, J112.1, J113.1, PWR37.1, R225.1, TP152.1, U38.6, U38.7
GND38: C77.1, C78.1, J115.1, J116.1, PWR38.1, R231.1, TP156.1, U39.6, U39.7
GND39: C79.1, C80.1, J118.1, J119.1, PWR39.1, R237.1, TP160.1, U40.6, U40.7
GND40: C81.1, C82.1, J121.1, J122.1, PWR40.1, R243.1, TP164.1, U41.6, U41.7
GND41: C83.1, C84.1, J124.1, J125.1, PWR41.1, R249.1, TP168.1, U42.6, U42.7
GND42: C85.1, C86.1, J127.1, J128.1, PWR42.1, R255.1, TP172.1, U43.6, U43.7
GND43: C87.1, C88.1, J130.1, J131.1, PWR43.1, R261.1, TP176.1, U44.6, U44.7
GND44: C89.1, C90.1, J133.1, J134.1, PWR44.1, R267.1, TP180.1, U45.6, U45.7
GND45: C91.1, C92.1, J136.1, J137.1, PWR45.1, R273.1, TP184.1, U46.6, U46.7
GND46: C93.1, C94.1, J139.1, J140.1, PWR46.1, R279.1, TP188.1, U47.6, U47.7
GND47: C95.1, C96.1, J142.1, J143.1, PWR47.1, R285.1, TP192.1, U48.6, U48.7
GND48: C97.1, C98.1, J145.1, J146.1, PWR48.1, R291.1, TP196.1, U49.6, U49.7
GND49: C99.1, C100.1, J148.1, J149.1, PWR49.1, R297.1, TP200.1, U50.6, U50.7
GND50: C101.1, C102.1, J151.1, J152.1, PWR50.1, R303.1, TP204.1, U51.6, U51.7
GND51: C103.1, C104.1, J154.1, J155.1, PWR51.1, R309.1, TP208.1, U52.6, U52.7
GND52: C105.1, C106.1, J157.1, J158.1, PWR52.1, R315.1, TP212.1, U53.6, U53.7
GND53: C107.1, C108.1, J160.1, J161.1, PWR53.1, R321.1, TP216.1, U54.6, U54.7
GND54: C109.1, C110.1, J163.1, J164.1, PWR54.1, R327.1, TP220.1, U55.6, U55.7
GND55: C111.1, C112.1, J166.1, J167.1, PWR55.1, R333.1, TP224.1, U56.6, U56.7
GND56: C113.1, C114.1, J169.1, J170.1, PWR56.1, R339.1, TP228.1, U57.6, U57.7
GND57: C115.1, C116.1, J172.1, J173.1, PWR57.1, R345.1, TP232.1, U58.6, U58.7
GND58: C117.1, C118.1, J175.1, J176.1, PWR58.1, R351.1, TP236.1, U59.6, U59.7
GND59: C119.1, C120.1, J178.1, J179.1, PWR59.1, R357.1, TP240.1, U60.6, U60.7
GND60: C121.1, C122.1, J181.1, J182.1, PWR60.1, R363.1, TP244.1, U61.6, U61.7
GND61: C123.1, C124.1, J184.1, J185.1, PWR61.1, R369.1, TP248.1, U62.6, U62.7
GND62: C125.1, C126.1, J187.1, J188.1, PWR62.1, R375.1, TP252.1, U63.6, U63.7
GND63: C127.1, C128.1, J190.1, J191.1, PWR63.1, R381.1, TP256.1, U64.6, U64.7
INT1: J3.1, U1.4
INT2: J6.1, U2.4
INT3: J9.1, U3.4
INT4: J12.1, U4.4
INT5: J15.1, U5.4
INT6: J18.1, U6.4
INT7: J21.1, U7.4
INT8: J24.1, U8.4
INT9: J27.1, U9.4
INT10: J30.1, U10.4
INT11: J33.1, U11.4
INT12: J36.1, U12.4
INT13: J39.1, U13.4
INT14: J42.1, U14.4
INT15: J45.1, U15.4
INT16: J48.1, U16.4
INT17: J51.1, U17.4
INT18: J54.1, U18.4
INT19: J57.1, U19.4
INT20: J60.1, U20.4
INT21: J63.1, U21.4
INT22: J66.1, U22.4
INT23: J69.1, U23.4
INT24: J72.1, U24.4
INT25: J75.1, U25.4
INT26: J78.1, U26.4
INT27: J81.1, U27.4
INT28: J84.1, U28.4
INT29: J87.1, U29.4
INT30: J90.1, U30.4
INT31: J93.1, U31.4
INT32: J96.1, U32.4
INT33: J99.1, U33.4
INT34: J102.1, U34.4
INT35: J105.1, U35.4
INT36: J108.1, U36.4
INT37: J111.1, U37.4
INT38: J114.1, U38.4
INT39: J117.1, U39.4
INT40: J120.1, U40.4
INT41: J123.1, U41.4
INT42: J126.1, U42.4
INT43: J129.1, U43.4
INT44: J132.1, U44.4
INT45: J135.1, U45.4
INT46: J138.1, U46.4
INT47: J141.1, U47.4
INT48: J144.1, U48.4
INT49: J147.1, U49.4
INT50: J150.1, U50.4
INT51: J153.1, U51.4
INT52: J156.1, U52.4
INT53: J159.1, U53.4
INT54: J162.1, U54.4
INT55: J165.1, U55.4
INT56: J168.1, U56.4
INT57: J171.1, U57.4
INT58: J174.1, U58.4
INT59: J177.1, U59.4
INT60: J180.1, U60.4
INT61: J183.1, U61.4
INT62: J186.1, U62.4
INT63: J189.1, U63.4
INT64: J192.1, U64.4
unnamed: I2C.1, R1.2
unnamed: I2C.3, R2.2
unnamed: D1.C, PWR.2
unnamed: D1.A, R4.1
unnamed: ADR.1, R5.1
unnamed: ADR.3, R3.2
unnamed: R6.1, U1.12
unnamed: I2C1.1, R7.2
unnamed: I2C1.3, R8.2
unnamed: ADR1.1, R11.1
unnamed: ADR1.3, R9.2
unnamed: R12.1, U2.12
unnamed: D2.C, PWR1.2
unnamed: D2.A, R10.1
unnamed: I2C2.1, R13.2
unnamed: I2C2.3, R14.2
unnamed: ADR2.1, R17.1
unnamed: ADR2.3, R15.2
unnamed: R18.1, U3.12
unnamed: D3.C, PWR2.2
unnamed: D3.A, R16.1
unnamed: I2C3.1, R19.2
unnamed: I2C3.3, R20.2
unnamed: ADR3.1, R23.1
unnamed: ADR3.3, R21.2
unnamed: R24.1, U4.12
unnamed: D4.C, PWR3.2
unnamed: D4.A, R22.1
unnamed: I2C4.1, R25.2
unnamed: I2C4.3, R26.2
unnamed: ADR4.1, R29.1
unnamed: ADR4.3, R27.2
unnamed: R30.1, U5.12
unnamed: D5.C, PWR4.2
unnamed: D5.A, R28.1
unnamed: I2C5.1, R31.2
unnamed: I2C5.3, R32.2
unnamed: ADR5.1, R35.1
unnamed: ADR5.3, R33.2
unnamed: R36.1, U6.12
unnamed: D6.C, PWR5.2
unnamed: D6.A, R34.1
unnamed: I2C6.1, R37.2
unnamed: I2C6.3, R38.2
unnamed: ADR6.1, R41.1
unnamed: ADR6.3, R39.2
unnamed: R42.1, U7.12
unnamed: D7.C, PWR6.2
unnamed: D7.A, R40.1
unnamed: I2C7.1, R43.2
unnamed: I2C7.3, R44.2
unnamed: ADR7.1, R47.1
unnamed: ADR7.3, R45.2
unnamed: R48.1, U8.12
unnamed: D8.C, PWR7.2
unnamed: D8.A, R46.1
unnamed: I2C8.1, R49.2
unnamed: I2C8.3, R50.2
unnamed: ADR8.1, R53.1
unnamed: ADR8.3, R51.2
unnamed: R54.1, U9.12
unnamed: D9.C, PWR8.2
unnamed: D9.A, R52.1
unnamed: I2C9.1, R55.2
unnamed: I2C9.3, R56.2
unnamed: ADR9.1, R59.1
unnamed: ADR9.3, R57.2
unnamed: R60.1, U10.12
unnamed: D10.C, PWR9.2
unnamed: D10.A, R58.1
unnamed: I2C10.1, R61.2
unnamed: I2C10.3, R62.2
unnamed: ADR10.1, R65.1
unnamed: ADR10.3, R63.2
unnamed: R66.1, U11.12
unnamed: D11.C, PWR10.2
unnamed: D11.A, R64.1
unnamed: I2C11.1, R67.2
unnamed: I2C11.3, R68.2
unnamed: ADR11.1, R71.1
unnamed: ADR11.3, R69.2
unnamed: R72.1, U12.12
unnamed: D12.C, PWR11.2
unnamed: D12.A, R70.1
unnamed: I2C12.1, R73.2
unnamed: I2C12.3, R74.2
unnamed: ADR12.1, R77.1
unnamed: ADR12.3, R75.2
unnamed: R78.1, U13.12
unnamed: D13.C, PWR12.2
unnamed: D13.A, R76.1
unnamed: I2C13.1, R79.2
unnamed: I2C13.3, R80.2
unnamed: ADR13.1, R83.1
unnamed: ADR13.3, R81.2
unnamed: R84.1, U14.12
unnamed: D14.C, PWR13.2
unnamed: D14.A, R82.1
unnamed: I2C14.1, R85.2
unnamed: I2C14.3, R86.2
unnamed: ADR14.1, R89.1
unnamed: ADR14.3, R87.2
unnamed: R90.1, U15.12
unnamed: D15.C, PWR14.2
unnamed: D15.A, R88.1
unnamed: I2C15.1, R91.2
unnamed: I2C15.3, R92.2
unnamed: ADR15.1, R95.1
unnamed: ADR15.3, R93.2
unnamed: R96.1, U16.12
unnamed: D16.C, PWR15.2
unnamed: D16.A, R94.1
unnamed: I2C16.1, R97.2
unnamed: I2C16.3, R98.2
unnamed: ADR16.1, R101.1
unnamed: ADR16.3, R99.2
unnamed: R102.1, U17.12
unnamed: D17.C, PWR16.2
unnamed: D17.A, R100.1
unnamed: I2C17.1, R103.2
unnamed: I2C17.3, R104.2
unnamed: ADR17.1, R107.1
unnamed: ADR17.3, R105.2
unnamed: R108.1, U18.12
unnamed: D18.C, PWR17.2
unnamed: D18.A, R106.1
unnamed: I2C18.1, R109.2
unnamed: I2C18.3, R110.2
unnamed: ADR18.1, R113.1
unnamed: ADR18.3, R111.2
unnamed: R114.1, U19.12
unnamed: D19.C, PWR18.2
unnamed: D19.A, R112.1
unnamed: I2C19.1, R115.2
unnamed: I2C19.3, R116.2
unnamed: ADR19.1, R119.1
unnamed: ADR19.3, R117.2
unnamed: R120.1, U20.12
unnamed: D20.C, PWR19.2
unnamed: D20.A, R118.1
unnamed: I2C20.1, R121.2
unnamed: I2C20.3, R122.2
unnamed: ADR20.1, R125.1
unnamed: ADR20.3, R123.2
unnamed: R126.1, U21.12
unnamed: D21.C, PWR20.2
unnamed: D21.A, R124.1
unnamed: I2C21.1, R127.2
unnamed: I2C21.3, R128.2
unnamed: ADR21.1, R131.1
unnamed: ADR21.3, R129.2
unnamed: R132.1, U22.12
unnamed: D22.C, PWR21.2
unnamed: D22.A, R130.1
unnamed: I2C22.1, R133.2
unnamed: I2C22.3, R134.2
unnamed: ADR22.1, R137.1
unnamed: ADR22.3, R135.2
unnamed: R138.1, U23.12
unnamed: D23.C, PWR22.2
unnamed: D23.A, R136.1
unnamed: I2C23.1, R139.2
unnamed: I2C23.3, R140.2
unnamed: ADR23.1, R143.1
unnamed: ADR23.3, R141.2
unnamed: R144.1, U24.12
unnamed: D24.C, PWR23.2
unnamed: D24.A, R142.1
unnamed: I2C24.1, R145.2
unnamed: I2C24.3, R146.2
unnamed: ADR24.1, R149.1
unnamed: ADR24.3, R147.2
unnamed: R150.1, U25.12
unnamed: D25.C, PWR24.2
unnamed: D25.A, R148.1
unnamed: I2C25.1, R151.2
unnamed: I2C25.3, R152.2
unnamed: ADR25.1, R155.1
unnamed: ADR25.3, R153.2
unnamed: R156.1, U26.12
unnamed: D26.C, PWR25.2
unnamed: D26.A, R154.1
unnamed: I2C26.1, R157.2
unnamed: I2C26.3, R158.2
unnamed: ADR26.1, R161.1
unnamed: ADR26.3, R159.2
unnamed: R162.1, U27.12
unnamed: D27.C, PWR26.2
unnamed: D27.A, R160.1
unnamed: I2C27.1, R163.2
unnamed: I2C27.3, R164.2
unnamed: ADR27.1, R167.1
unnamed: ADR27.3, R165.2
unnamed: R168.1, U28.12
unnamed: D28.C, PWR27.2
unnamed: D28.A, R166.1
unnamed: I2C28.1, R169.2
unnamed: I2C28.3, R170.2
unnamed: ADR28.1, R173.1
unnamed: ADR28.3, R171.2
unnamed: R174.1, U29.12
unnamed: D29.C, PWR28.2
unnamed: D29.A, R172.1
unnamed: I2C29.1, R175.2
unnamed: I2C29.3, R176.2
unnamed: ADR29.1, R179.1
unnamed: ADR29.3, R177.2
unnamed: R180.1, U30.12
unnamed: D30.C, PWR29.2
unnamed: D30.A, R178.1
unnamed: I2C30.1, R181.2
unnamed: I2C30.3, R182.2
unnamed: ADR30.1, R185.1
unnamed: ADR30.3, R183.2
unnamed: R186.1, U31.12
unnamed: D31.C, PWR30.2
unnamed: D31.A, R184.1
unnamed: I2C31.1, R187.2
unnamed: I2C31.3, R188.2
unnamed: ADR31.1, R191.1
unnamed: ADR31.3, R189.2
unnamed: R192.1, U32.12
unnamed: D32.C, PWR31.2
unnamed: D32.A, R190.1
unnamed: I2C32.1, R193.2
unnamed: I2C32.3, R194.2
unnamed: ADR32.1, R197.1
unnamed: ADR32.3, R195.2
unnamed: R198.1, U33.12
unnamed: D33.C, PWR32.2
unnamed: D33.A, R196.1
unnamed: I2C33.1, R199.2
unnamed: I2C33.3, R200.2
unnamed: ADR33.1, R203.1
unnamed: ADR33.3, R201.2
unnamed: R204.1, U34.12
unnamed: D34.C, PWR33.2
unnamed: D34.A, R202.1
unnamed: I2C34.1, R205.2
unnamed: I2C34.3, R206.2
unnamed: ADR34.1, R209.1
unnamed: ADR34.3, R207.2
unnamed: R210.1, U35.12
unnamed: D35.C, PWR34.2
unnamed: D35.A, R208.1
unnamed: I2C35.1, R211.2
unnamed: I2C35.3, R212.2
unnamed: ADR35.1, R215.1
unnamed: ADR35.3, R213.2
unnamed: R216.1, U36.12
unnamed: D36.C, PWR35.2
unnamed: D36.A, R214.1
unnamed: I2C36.1, R217.2
unnamed: I2C36.3, R218.2
unnamed: ADR36.1, R221.1
unnamed: ADR36.3, R219.2
unnamed: R222.1, U37.12
unnamed: D37.C, PWR36.2
unnamed: D37.A, R220.1
unnamed: I2C37.1, R223.2
unnamed: I2C37.3, R224.2
unnamed: ADR37.1, R227.1
unnamed: ADR37.3, R225.2
unnamed: R228.1, U38.12
unnamed: D38.C, PWR37.2
unnamed: D38.A, R226.1
unnamed: I2C38.1, R229.2
unnamed: I2C38.3, R230.2
unnamed: ADR38.1, R233.1
unnamed: ADR38.3, R231.2
unnamed: R234.1, U39.12
unnamed: D39.C, PWR38.2
unnamed: D39.A, R232.1
unnamed: I2C39.1, R235.2
unnamed: I2C39.3, R236.2
unnamed: ADR39.1, R239.1
unnamed: ADR39.3, R237.2
unnamed: R240.1, U40.12
unnamed: D40.C, PWR39.2
unnamed: D40.A, R238.1
unnamed: I2C40.1, R241.2
unnamed: I2C40.3, R242.2
unnamed: ADR40.1, R245.1
unnamed: ADR40.3, R243.2
unnamed: R246.1, U41.12
unnamed: D41.C, PWR40.2
unnamed: D41.A, R244.1
unnamed: I2C41.1, R247.2
unnamed: I2C41.3, R248.2
unnamed: ADR41.1, R251.1
unnamed: ADR41.3, R249.2
unnamed: R252.1, U42.12
unnamed: D42.C, PWR41.2
unnamed: D42.A, R250.1
unnamed: I2C42.1, R253.2
unnamed: I2C42.3, R254.2
unnamed: ADR42.1, R257.1
unnamed: ADR42.3, R255.2
unnamed: R258.1, U43.12
unnamed: D43.C, PWR42.2
unnamed: D43.A, R256.1
unnamed: I2C43.1, R259.2
unnamed: I2C43.3, R260.2
unnamed: ADR43.1, R263.1
unnamed: ADR43.3, R261.2
unnamed: R264.1, U44.12
unnamed: D44.C, PWR43.2
unnamed: D44.A, R262.1
unnamed: I2C44.1, R265.2
unnamed: I2C44.3, R266.2
unnamed: ADR44.1, R269.1
unnamed: ADR44.3, R267.2
unnamed: R270.1, U45.12
unnamed: D45.C, PWR44.2
unnamed: D45.A, R268.1
unnamed: I2C45.1, R271.2
unnamed: I2C45.3, R272.2
unnamed: ADR45.1, R275.1
unnamed: ADR45.3, R273.2
unnamed: R276.1, U46.12
unnamed: D46.C, PWR45.2
unnamed: D46.A, R274.1
unnamed: I2C46.1, R277.2
unnamed: I2C46.3, R278.2
unnamed: ADR46.1, R281.1
unnamed: ADR46.3, R279.2
unnamed: R282.1, U47.12
unnamed: D47.C, PWR46.2
unnamed: D47.A, R280.1
unnamed: I2C47.1, R283.2
unnamed: I2C47.3, R284.2
unnamed: ADR47.1, R287.1
unnamed: ADR47.3, R285.2
unnamed: R288.1, U48.12
unnamed: D48.C, PWR47.2
unnamed: D48.A, R286.1
unnamed: I2C48.1, R289.2
unnamed: I2C48.3, R290.2
unnamed: ADR48.1, R293.1
unnamed: ADR48.3, R291.2
unnamed: R294.1, U49.12
unnamed: D49.C, PWR48.2
unnamed: D49.A, R292.1
unnamed: I2C49.1, R295.2
unnamed: I2C49.3, R296.2
unnamed: ADR49.1, R299.1
unnamed: ADR49.3, R297.2
unnamed: R300.1, U50.12
unnamed: D50.C, PWR49.2
unnamed: D50.A, R298.1
unnamed: I2C50.1, R301.2
unnamed: I2C50.3, R302.2
unnamed: ADR50.1, R305.1
unnamed: ADR50.3, R303.2
unnamed: R306.1, U51.12
unnamed: D51.C, PWR50.2
unnamed: D51.A, R304.1
unnamed: I2C51.1, R307.2
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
